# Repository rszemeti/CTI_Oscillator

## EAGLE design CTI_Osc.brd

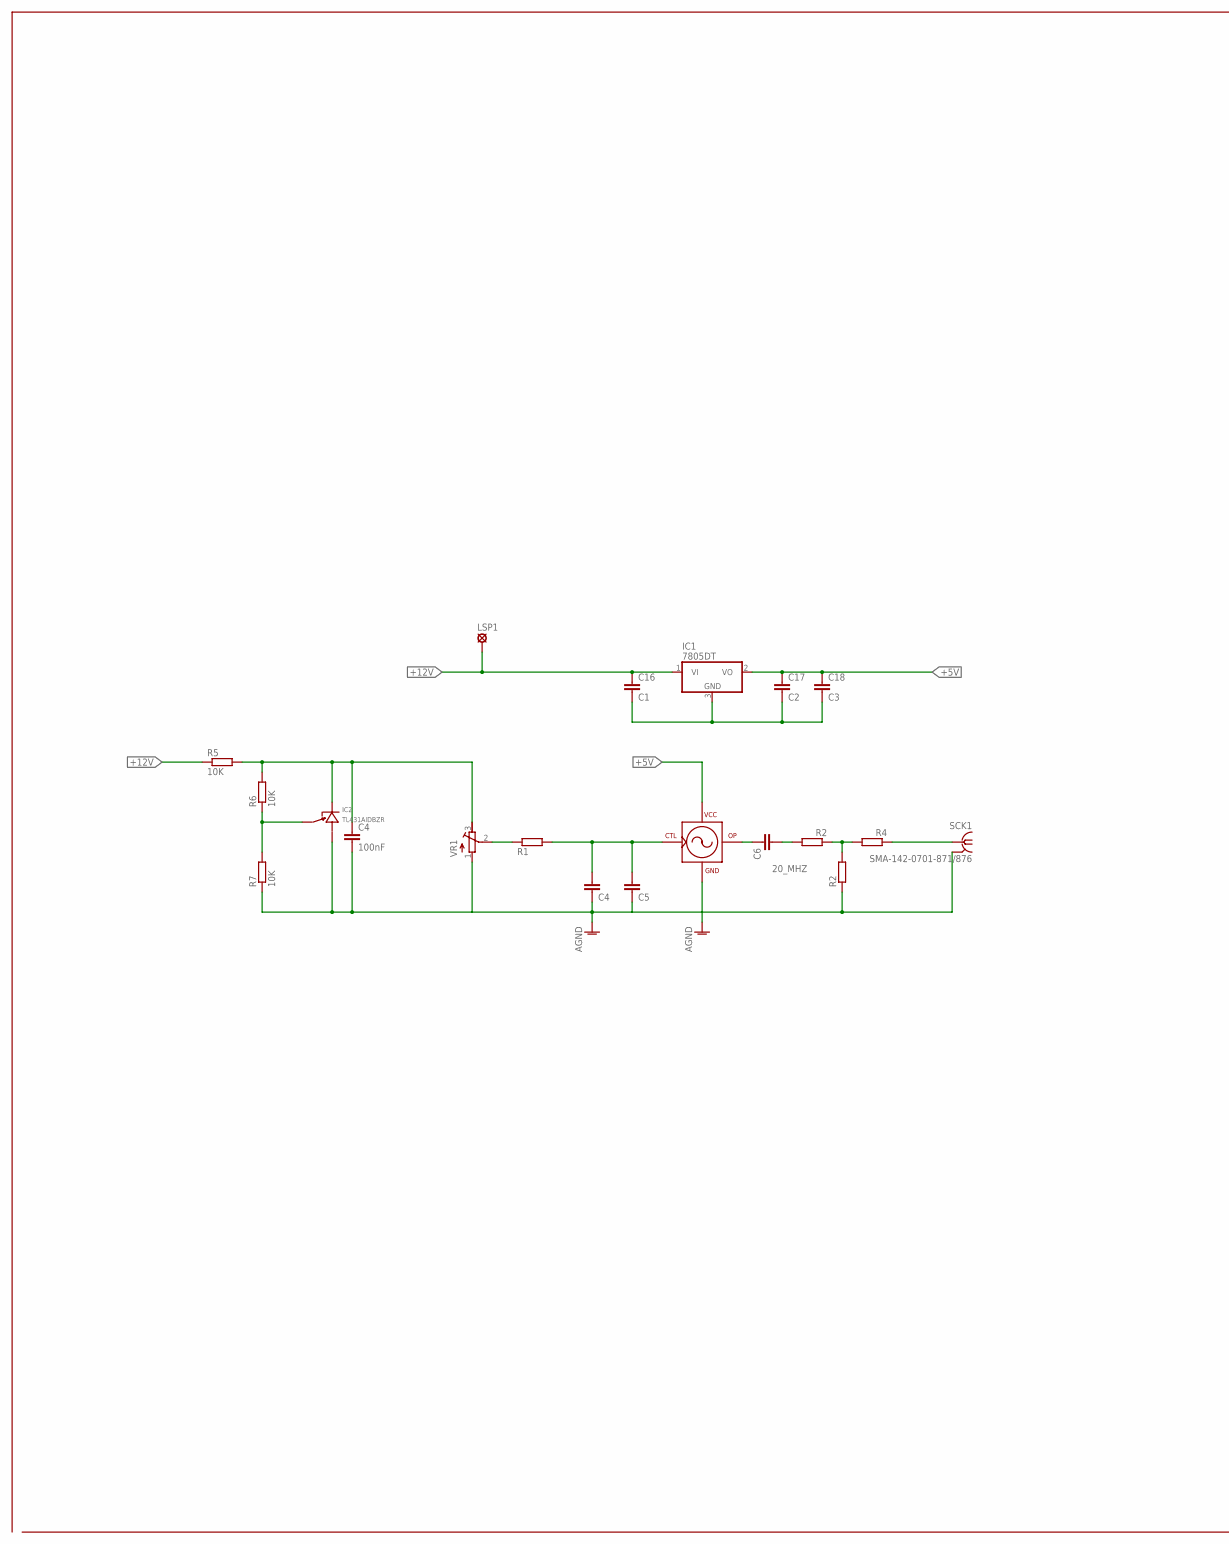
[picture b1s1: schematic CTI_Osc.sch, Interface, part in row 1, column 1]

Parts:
C4: 100nF; C0603
C16: C1; C0805
C17: C2; C0805
C18: C3; C0805
C24: C4; C0603
C25: C5; C0603
C28: C6; C0603
IC1: 7805DT; TO252
IC2: TL431AIDBZR; SOT23L
LSP1: LSP13
OSC1: CTI_OSC
R1: R2; R0603
R2: R3; R0603
R3: R4; R0603
R5, R6, R7: 10K; R0603
R13: R1; R0603
SCK1: SMA-142-0701-871/876; J502-ND-142-0701-871/876
VR2: VR1; RTRIM64Y

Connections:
20_MHZ: C28.2, OSC1.OUT (OP)
+5V: C17.1, C18.1, IC1.2 (VO), OSC1.VCC
+5V_PRECISION: C4.1, IC2.G (CATHODE), R5.2, R6.2, VR2.3 (A)
+12V: C16.1, IC1.1 (VI), LSP1.MP, R5.1
GND: C4.2, C16.2, C17.2, C18.2, C24.2, C25.2, IC1.3 (GND), IC2.D (ANODE), OSC1.GND, R2.1, R7.1, SCK1.G@1 (GND), SCK1.G@2 (GND), SCK1.G@3 (GND), SCK1.G@4 (GND), VR2.1 (E)
unnamed: C28.1, R1.2
unnamed: R1.1, R2.2, R3.2
unnamed: R3.1, SCK1.1
unnamed: R13.1, VR2.2 (S)
unnamed: C24.1, C25.1, OSC1.REF (CTRL), R13.2
unnamed: IC2.S (CTRL), R6.1, R7.2

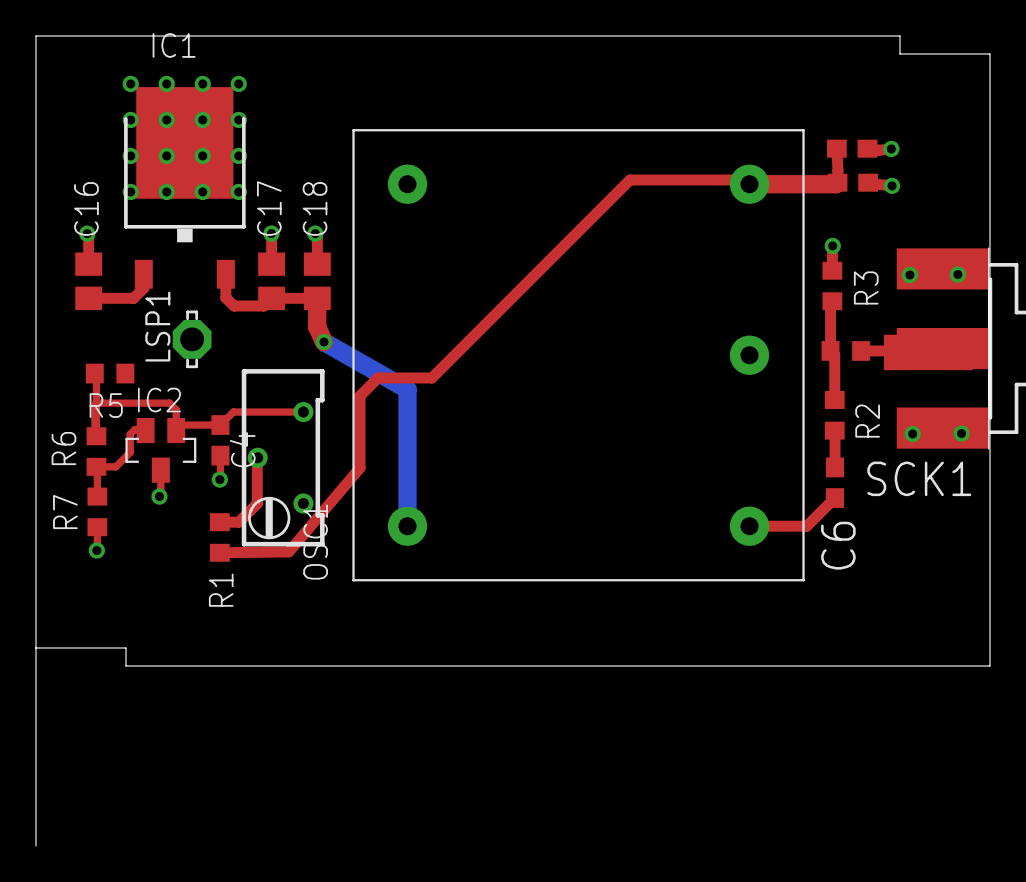
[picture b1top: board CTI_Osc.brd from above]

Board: 4 copper layers, 53.0 x 45.0 mm, 20 parts (0 on the bottom side), 11 nets.

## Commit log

2022-11-26 Remove backups
    delete unwanted backup files
2022-11-26 Create LICENSE
2022-11-26 First release gerbers
2022-11-28 V1 release
    Added a TL431C for precision control of the freq set pin.

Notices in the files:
parts and their libraries:
Document: This design is licensed under a Creative Commons Attribution-ShareAlike
Document: 3.0 Unported License: http://creativecommons.org/licenses/by-sa/3.0
